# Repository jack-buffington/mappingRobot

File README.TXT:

This readme was last updated on March 20 2022.

This repository will eventually contain all of the files necessary to make a mapping robot that can map its 
environment using a 2D lidar-like sensor.  At the time of writing this README, the project is 
ongoing.  Eventual goals of this project are:

* Have the robot autonomously map its environment using a RPlidar A2 module.  
* Know when it is done mapping its environment. 
* Do so using ROS.  
* With only a few minor exceptions, run exclusively my own code.
* Have the capability to connect to the robot using a remote computer which can view the current state of the
map as well as to take direct control of the robot.  

The robot system will consist of three processors.  The first is the remote computer which does no 
major computation.  It will be for the user to view the map and to control the state of the robot if necessary.  
The second is an onboard processor that will do the heavy lifting and which holds 
the most up-to-date map.  The third is a microcontroller that handles low-level tasks such as driving the motors, 
reading sensors, and controllng the power to the motors, CPU, and itself. 

Power is supplied to the robot from an off-the-shelf battery pack for Dewalt cordless tools.  

It its current state, the MCU code is pretty much fully functional.  I will likely update it at some point to
read one or more downward-looking range finders so that it doesn't attempt suicide by driving down steps.  It currently
can do the following:
   * Read the battery voltage, display it on the OLED display, and send the voltage to the CPU
   * Read the encoders attached to the motors and send their values to the CPU
   * Drive the motors with a closed-loop velocity controller
   * Play beeps
   * Control the power to the CPU, motors, and itself
   * Communicate through two serial ports.  One to the CPU and one connected to the programming port.
  
The CPU code has:
   RPlidar node - controls a RPlidar A2 and reads its data.  This data is conditionally published based on a divider that 
       Allows it to send every N scans.  
   MCU node - Subscribes to a few topics which can be forwarded to the MCU and publishes a couple others which repeat 
       messages received from the MCU in a ROS-friendly format.  

The Remote computer code has:
   lidar viewer - Ideally I would use RVIZ to see the lidar data but either I don't yet know how to use RVIZ or I have it
	misconfigured so I wrote a quick and dirty program to display the scans.  
   joystick driving node - Lets you control the robot with a joystick if you have teleop_twist_joy installed on your system.

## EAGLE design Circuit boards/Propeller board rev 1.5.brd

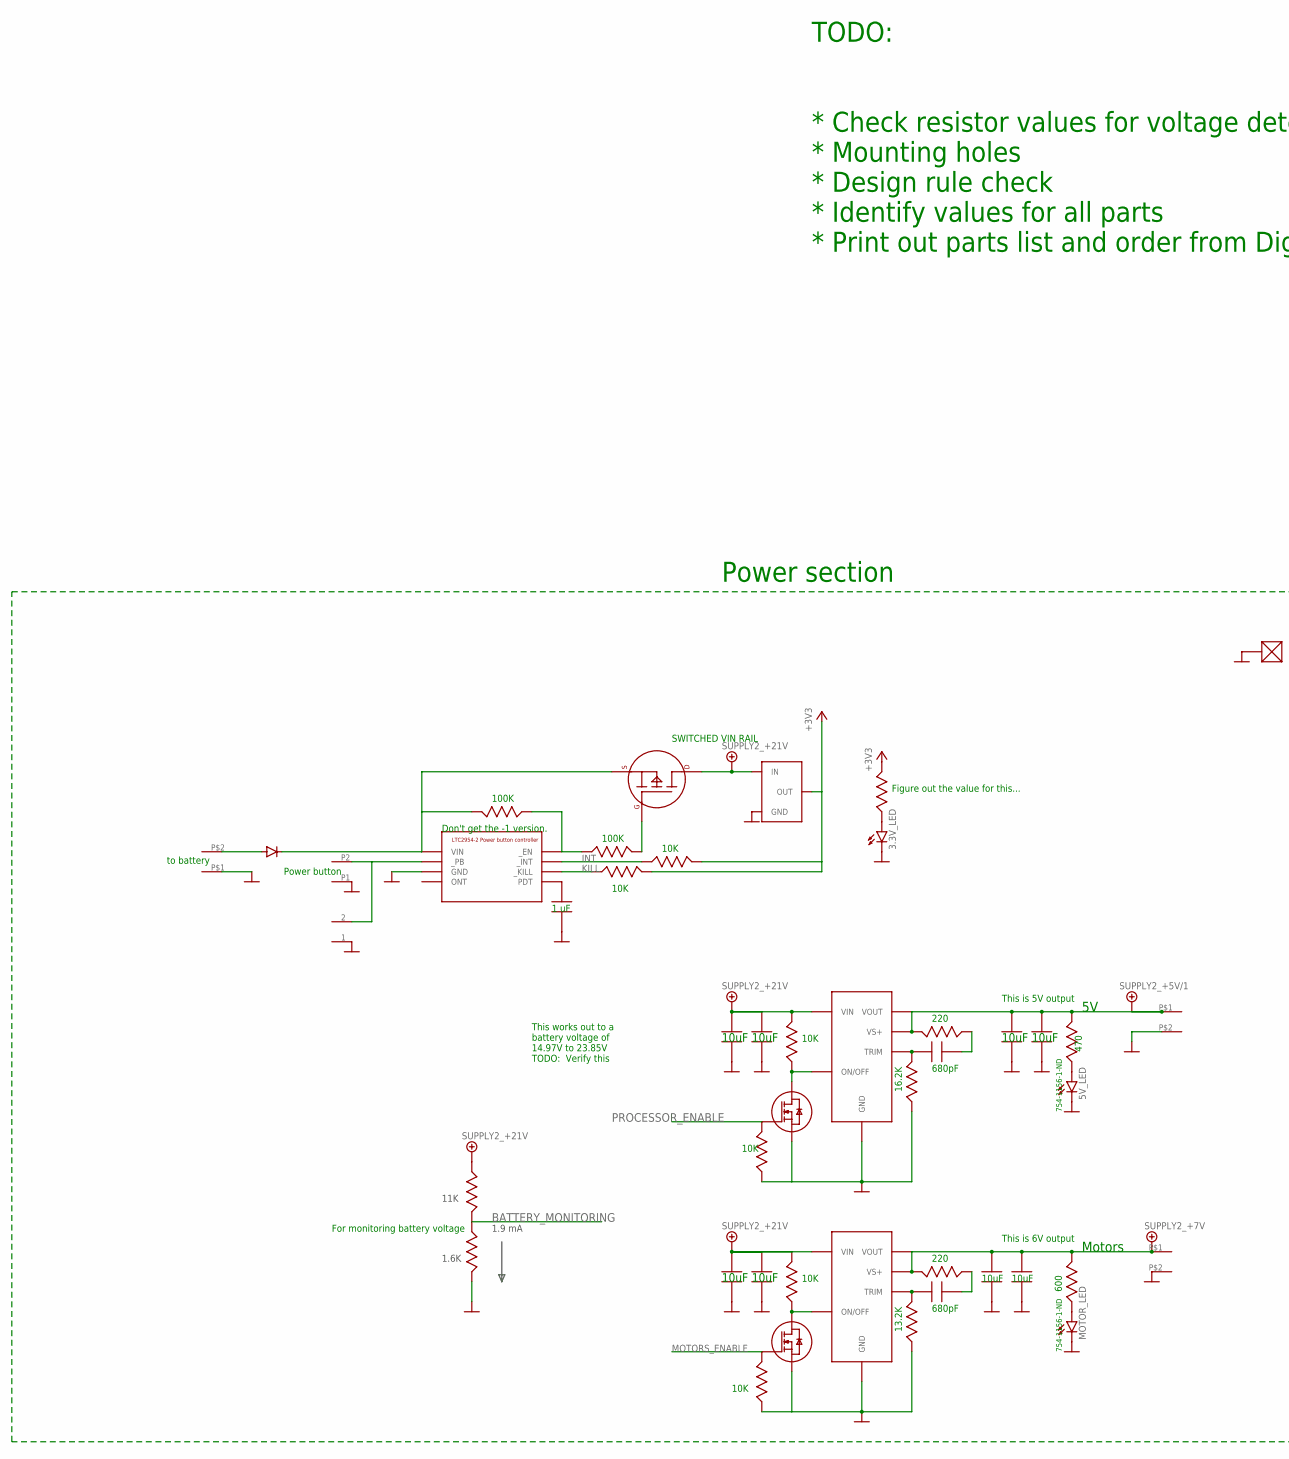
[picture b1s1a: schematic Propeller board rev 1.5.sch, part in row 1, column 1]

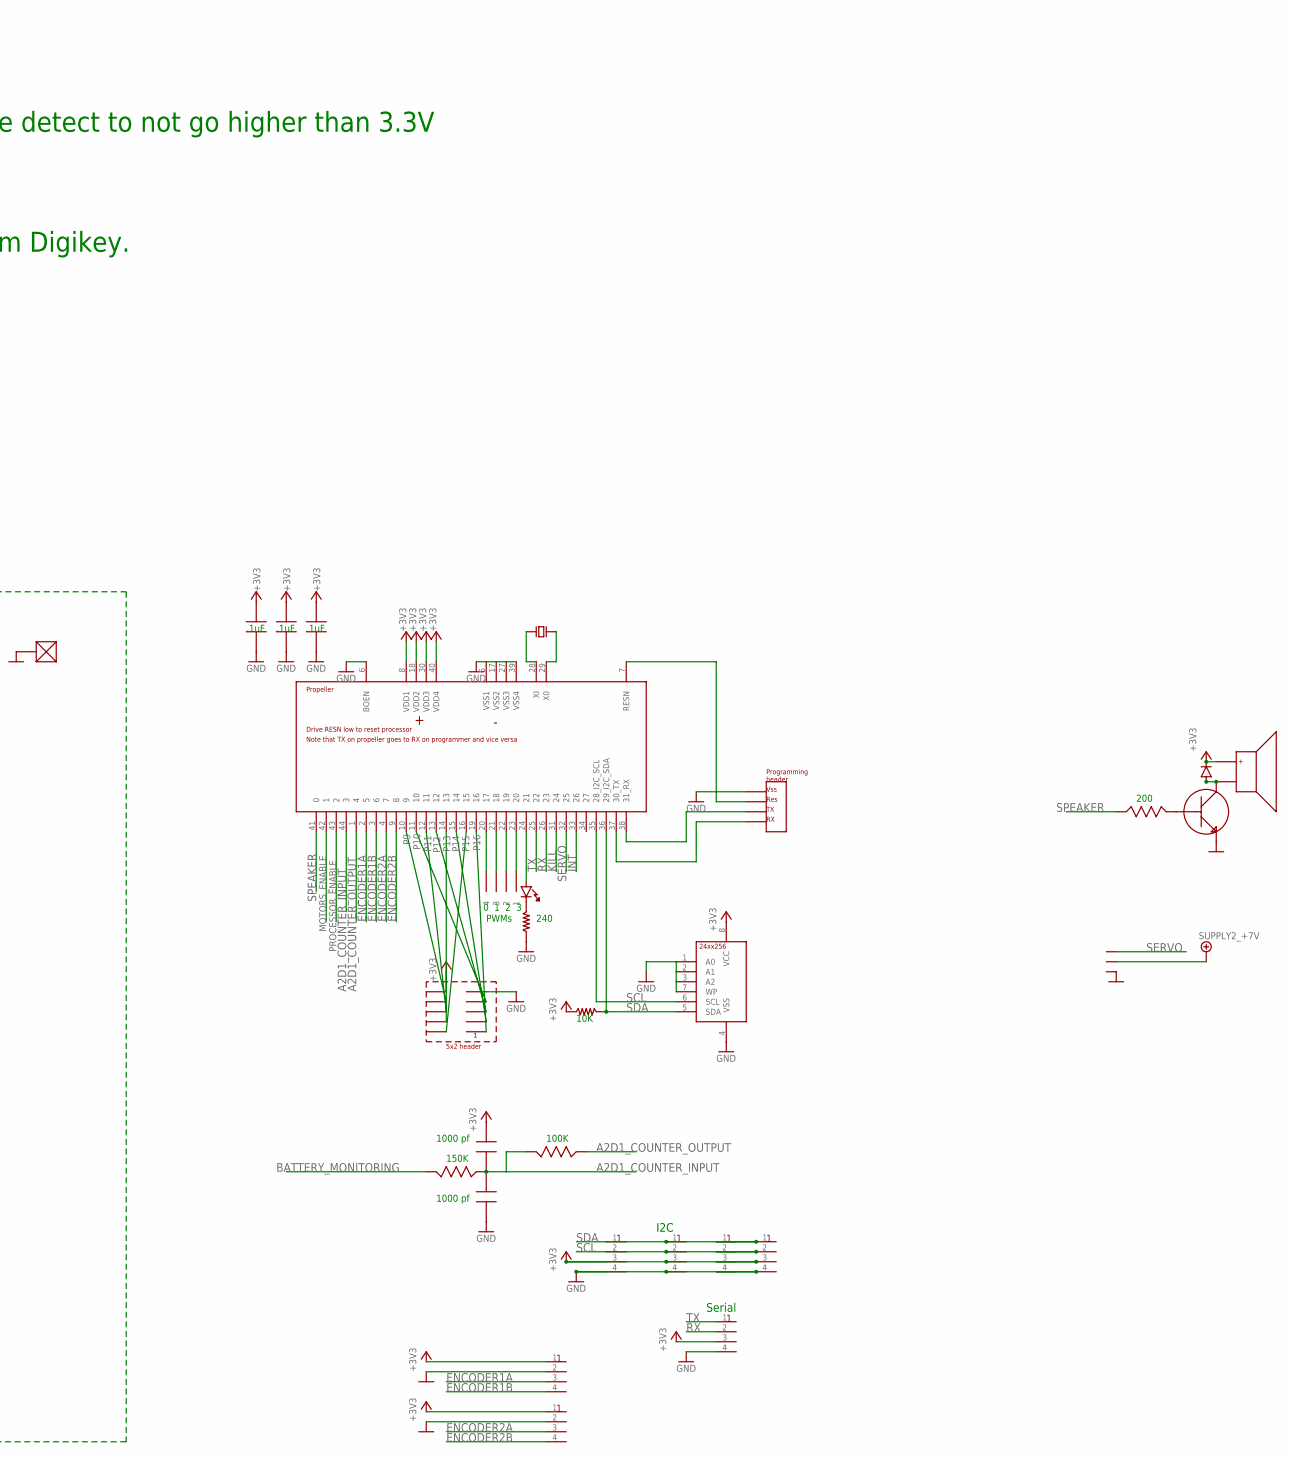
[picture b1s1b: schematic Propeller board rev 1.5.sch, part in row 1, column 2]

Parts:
3.3V_LED, 5V_LED: LED_LEDSML1206; LED_SML1206
3V3_REGULATOR_FOR_PROPELLER: VOLTAGE_REGULATOR_3_TERMINALXP_POWER_VR05_SERIES; VR05_SERIES_VREG
5V_C_680PF: 680pf; JACK_0805
5V_LED_R1, 5V_LED_R2: 470; JACK_0805
5V_REGULATOR_PULLUP: 10K; JACK_0805
5V_R_220: 220; JACK_0805
BATTERY_VOLTAGE_DIVIDER_HIGH: 11K; JACK_0805
BATTERY_VOLTAGE_DIVIDER_LOW: 1.6K; JACK_0805
MOTOR_C_680PF: 680pf; JACK_0805
MOTOR_ENABLE_MOSFET, MOTOR_ENABLE_MOSFET1: JACK_MOSFET_N_CHANNELBSS138LCT-ND; JACK_SOT23
MOTOR_LED: LED_LEDSML1206; LED_SML1206
MOTOR_LED_R: 600; JACK_0805
MOTOR_MOSFET_PULLDOWN: 10K; JACK_0805
MOTOR_PULLUP, MOTOR_PULLUP2: 10K; JACK_0805
MOTOR_R_220: 220; JACK_0805
MOTOR_TRIM: 13.2K; JACK_0805
R1: 240; 805_SMD
R25: 10k; 805_SMD
RTRIM_5V: 16.2K; JACK_0805
U1: PARALLAX_PROPELLER; 44LQFP
U2: EEPROM_24XX256; 8_MSOP
U$1: CONNECTOR_2_PINJST_PH_SERIES; JST_2_PIN_PH_SERIES
U$2, U$6, U$13: JACK_SCREW_TERMINAL_2_CONDUCTORAMP-282837-2; JACK_AMP-282837-2
U$3: POWER_CONTROLLER_LTC2954-2TSOT-23-8; TSOT-23-8
U$4, U$17: JACK_DC_TO_DC_VARIABLE_555-1172-1-ND; JACK_DC2DC_555-1172-1-ND
U$5: 1uf; 0805
U$7, U$9, U$44: 100K; 0805
U$10, U$27: 10K; 0805
U$11: 1000pF or 1nF; 0805
U$12: MOSFET_P_CHANNELSI4431CDY; SO8
U$14, U$16, U$18: .1uf; 0805
U$15: CRYSTAL8X4.5_PACKAGE; CRYSTAL_NX8045GB-5MHZ-STD-CSF-3
U$19: TEST_POINT; KEYSTONE_ELECTRONICS_5118_TEST_POINT
U$20: LED0805; 0805
U$21: HEADER_4_PIN_.1"; FOUR_.1"_HOLES
U$22: HEADER_5X2; HEADER_5X2_.1"_SPACING
U$23, U$24, U$25, U$45, U$46, U$47, U$49: CONNECTOR_4_PINJST_PH_SERIES; JST_4_PIN_PH_SERIES
U$26: CONNECTOR_2_PINJST_.1"; JST_2_PIN_.1"
U$28, U$29: 10uF; 1210
U$30, U$31, U$32, U$33, U$40, U$41: 10uf; 1210
U$34: SPEAKERGT-0950RP3; AUDIO_TRANSDUCER_GT-0950RP3
U$35: DIODESOD523F; SOD523F
U$36: TRANSISTOR_NPNMMBT3904; SOT23
U$37: 200; 0805
U$38: CONNECTOR_3_PIN.1"SPACING; THREE_.1"_HOLES
U$39: DIODEPOWER_DI15; POWER_DI15
U$42: 1000pf or 1 nF; 0805
U$43: 150K; 0805
U$48: PROPELLER_PROGRAMMING_HEADERHOLES; FOUR_.1"HOLES

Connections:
+3V3: 3V3_REGULATOR_FOR_PROPELLER.VOUT (OUT), 5V_LED_R2.P$3, R25.P$1, U1.8 (VDD1), U1.18 (VDD2), U1.30 (VDD3), U1.40 (VDD4), U2.8 (VCC), U$10.C2, U$11.C2 (2-), U$14.C2 (2-), U$16.C2 (2-), U$18.C2 (2-), U$22.P10 (10), U$23.3, U$24.3, U$25.3, U$27.C2, U$34.+, U$35.C, U$45.3, U$46.1, U$47.3, U$49.1
+5V/1: 5V_LED_R1.P$3, 5V_R_220.P$3, U$2.P$1, U$4.VOUT, U$4.VS+, U$30.2 (2-), U$33.2 (2-)
+7V: MOTOR_LED_R.P$3, MOTOR_R_220.P$3, U$13.P$1, U$17.VOUT, U$17.VS+, U$32.2 (2-), U$38.2, U$40.2 (2-)
+21V: 3V3_REGULATOR_FOR_PROPELLER.VIN (IN), 5V_REGULATOR_PULLUP.P$3, BATTERY_VOLTAGE_DIVIDER_HIGH.P$2, MOTOR_PULLUP.P$3, U$4.VIN, U$12.5 (D), U$12.6 (D), U$12.7 (D), U$12.8 (D), U$17.VIN, U$28.2 (2-), U$29.2 (2-), U$31.2 (2-), U$41.2 (2-)
A2D1_COUNTER_INPUT: U1.44 (3), U$11.A1 (1+), U$42.C2 (2-), U$43.A1, U$44.C2
A2D1_COUNTER_OUTPUT: U1.1 (4), U$44.A1
BATTERY_MONITORING: BATTERY_VOLTAGE_DIVIDER_HIGH.P$3, BATTERY_VOLTAGE_DIVIDER_LOW.P$2, U$43.C2
ENCODER1A: U1.2 (5), U$46.3
ENCODER1B: U1.3 (6), U$46.4
ENCODER2A: U1.4 (7), U$49.3
ENCODER2B: U1.9 (8), U$49.4
GND: 3.3V_LED.C, 3V3_REGULATOR_FOR_PROPELLER.GND, 5V_LED.C, BATTERY_VOLTAGE_DIVIDER_LOW.P$3, MOTOR_ENABLE_MOSFET.2 (S), MOTOR_ENABLE_MOSFET1.2 (S), MOTOR_LED.C, MOTOR_MOSFET_PULLDOWN.P$2, MOTOR_PULLUP2.P$2, MOTOR_TRIM.P$2, R1.P$1, RTRIM_5V.P$2, U1.5 (VSS1), U1.6 (BOEN), U1.17 (VSS2), U1.27 (VSS3), U1.39 (VSS4), U2.1 (A0), U2.2 (A1), U2.3 (A2), U2.4 (VSS), U2.7 (WP), U$1.P1, U$2.P$2, U$3.4 (GND), U$4.GND, U$5.A1 (1+), U$6.P$1, U$13.P$2, U$14.A1 (1+), U$16.A1 (1+), U$17.GND, U$18.A1 (1+), U$19.P1, U$22.P9 (9), U$23.4, U$24.4, U$25.4, U$26.1, U$28.1 (1+), U$29.1 (1+), U$30.1 (1+), U$31.1 (1+), U$32.1 (1+), U$33.1 (1+), U$36.2 (E), U$38.1, U$40.1 (1+), U$41.1 (1+), U$42.A1 (1+), U$45.4, U$46.2, U$47.4, U$48.1 (VSS), U$49.2
INT: U1.33 (26), U$3.5 (_INT), U$10.A1
KILL: U1.31 (24), U$3.8 (_KILL), U$27.A1
MOTORS_ENABLE: MOTOR_ENABLE_MOSFET.1 (G), MOTOR_MOSFET_PULLDOWN.P$3, U1.42 (1)
unnamed: U1.7 (RESN), U$48.2 (RES)
unnamed: U1.24 (21), U$20.A1 (A)
unnamed: U$1.P2, U$3.2 (_PB), U$26.2
unnamed: MOTOR_LED.A, MOTOR_LED_R.P$2
unnamed: U$3.1 (VIN), U$7.C2, U$12.1 (S), U$12.2 (S), U$12.3 (S), U$39.3 (C)
unnamed: U$3.7 (PDT), U$5.C2 (2-)
unnamed: U$3.6 (_EN), U$7.A1, U$9.A1
unnamed: MOTOR_ENABLE_MOSFET.3 (D), MOTOR_PULLUP.P$2, U$17.ON/OFF
unnamed: U$9.C2, U$12.4 (G)
unnamed: R1.P$2, U$20.C2 (C)
unnamed: U1.23 (20), U$21.1
unnamed: U1.22 (19), U$21.2
unnamed: U1.21 (18), U$21.3
unnamed: U$34.-, U$35.A, U$36.3 (C)
unnamed: U$36.1 (B), U$37.C2
unnamed: U1.20 (17), U$21.4
unnamed: 5V_C_680PF.P$3 (2), RTRIM_5V.P$3, U$4.TRIM
unnamed: 3.3V_LED.A, 5V_LED_R2.P$2
unnamed: U$6.P$2, U$39.1 (A), U$39.2 (A)
unnamed: U1.38 (31_RX), U$48.3 (TX)
unnamed: 5V_LED.A, 5V_LED_R1.P$2
unnamed: 5V_REGULATOR_PULLUP.P$2, MOTOR_ENABLE_MOSFET1.3 (D), U$4.ON/OFF
unnamed: 5V_C_680PF.P$2 (1), 5V_R_220.P$2
unnamed: MOTOR_C_680PF.P$3 (2), MOTOR_TRIM.P$3, U$17.TRIM
unnamed: MOTOR_C_680PF.P$2 (1), MOTOR_R_220.P$2
unnamed: U1.37 (30_TX), U$48.4 (RX)
unnamed: U1.28 (XI), U$15.1
unnamed: U1.29 (X0), U$15.2
P9: U1.10 (9), U$22.P8 (8)
P10: U1.11 (10), U$22.P7 (7)
P11: U1.12 (11), U$22.P6 (6)
P12: U1.13 (12), U$22.P5 (5)
P13: U1.14 (13), U$22.P4 (4)
P14: U1.15 (14), U$22.P3 (3)
P15: U1.16 (15), U$22.P2 (2)
P16: U1.19 (16), U$22.P1 (1)
PROCESSOR_ENABLE: MOTOR_ENABLE_MOSFET1.1 (G), MOTOR_PULLUP2.P$3, U1.43 (2)
RX: U1.26 (23), U$47.2
SCL: U1.35 (28_I2C_SCL), U2.6 (SCL), U$23.2, U$24.2, U$25.2, U$45.2
SDA: R25.P$2, U1.36 (29_I2C_SDA), U2.5 (SDA), U$23.1, U$24.1, U$25.1, U$45.1
SERVO: U1.32 (25), U$38.3
SPEAKER: U1.41 (0), U$37.A1
TX: U1.25 (22), U$47.1

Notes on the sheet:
to battery
For monitoring battery voltage
Motors
Power section
754-1156-1-ND
11K
1.6K
1.9 mA
This works out to a battery voltage of 14.97V to 23.85V TODO: Verify this
Power button
10K
This is 6V output
This is 5V output
13.2K
16.2K
220
680pF
470
600
SWITCHED VIN RAIL
100K
TODO: * Check resistor values for voltage detect to not go higher than 3.3V * Mounting holes * Design rule check * Identify values for all parts * Print out parts list and order from Digikey.
10uF
I2C
Serial
PWMs
150K
Figure out the value for this...
0 1 2 3
1000 pf
240
200
1 uF
.1uF
Don't get the -1 version.

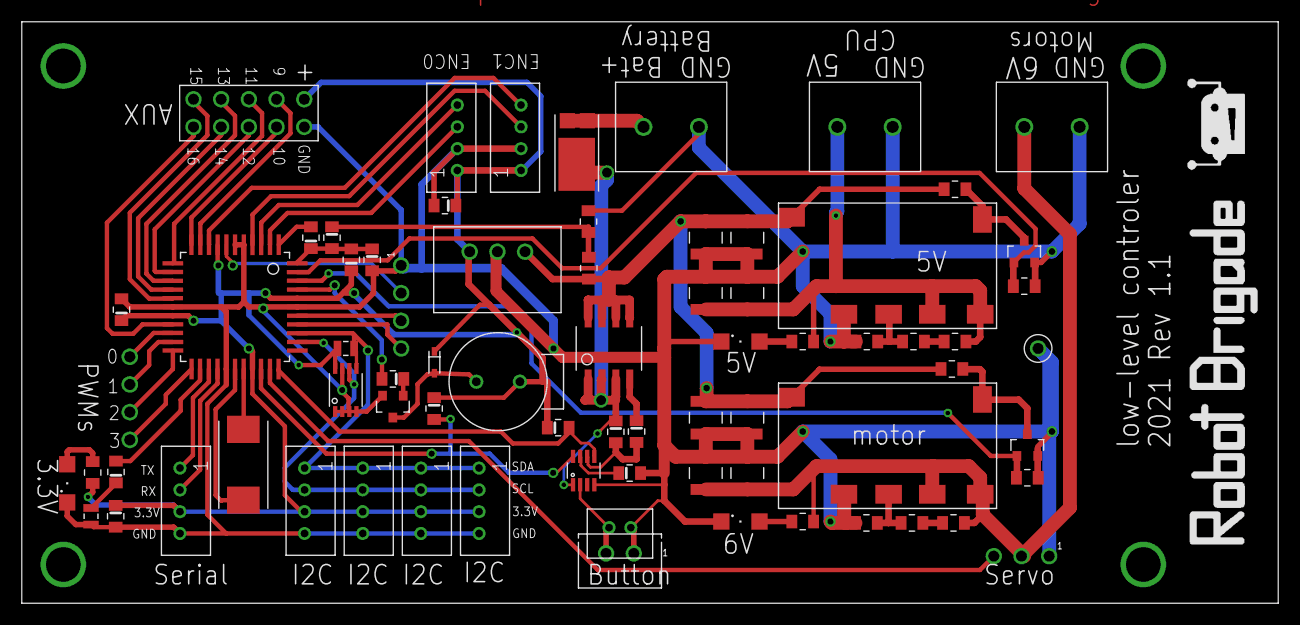
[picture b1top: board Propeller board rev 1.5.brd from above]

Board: 2 copper layers, 115.2 x 53.3 mm, 74 parts (0 on the bottom side), 58 nets.

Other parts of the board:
U$8: ROBOT_BRIGADE_LOGO_AND_TEXT_.2"

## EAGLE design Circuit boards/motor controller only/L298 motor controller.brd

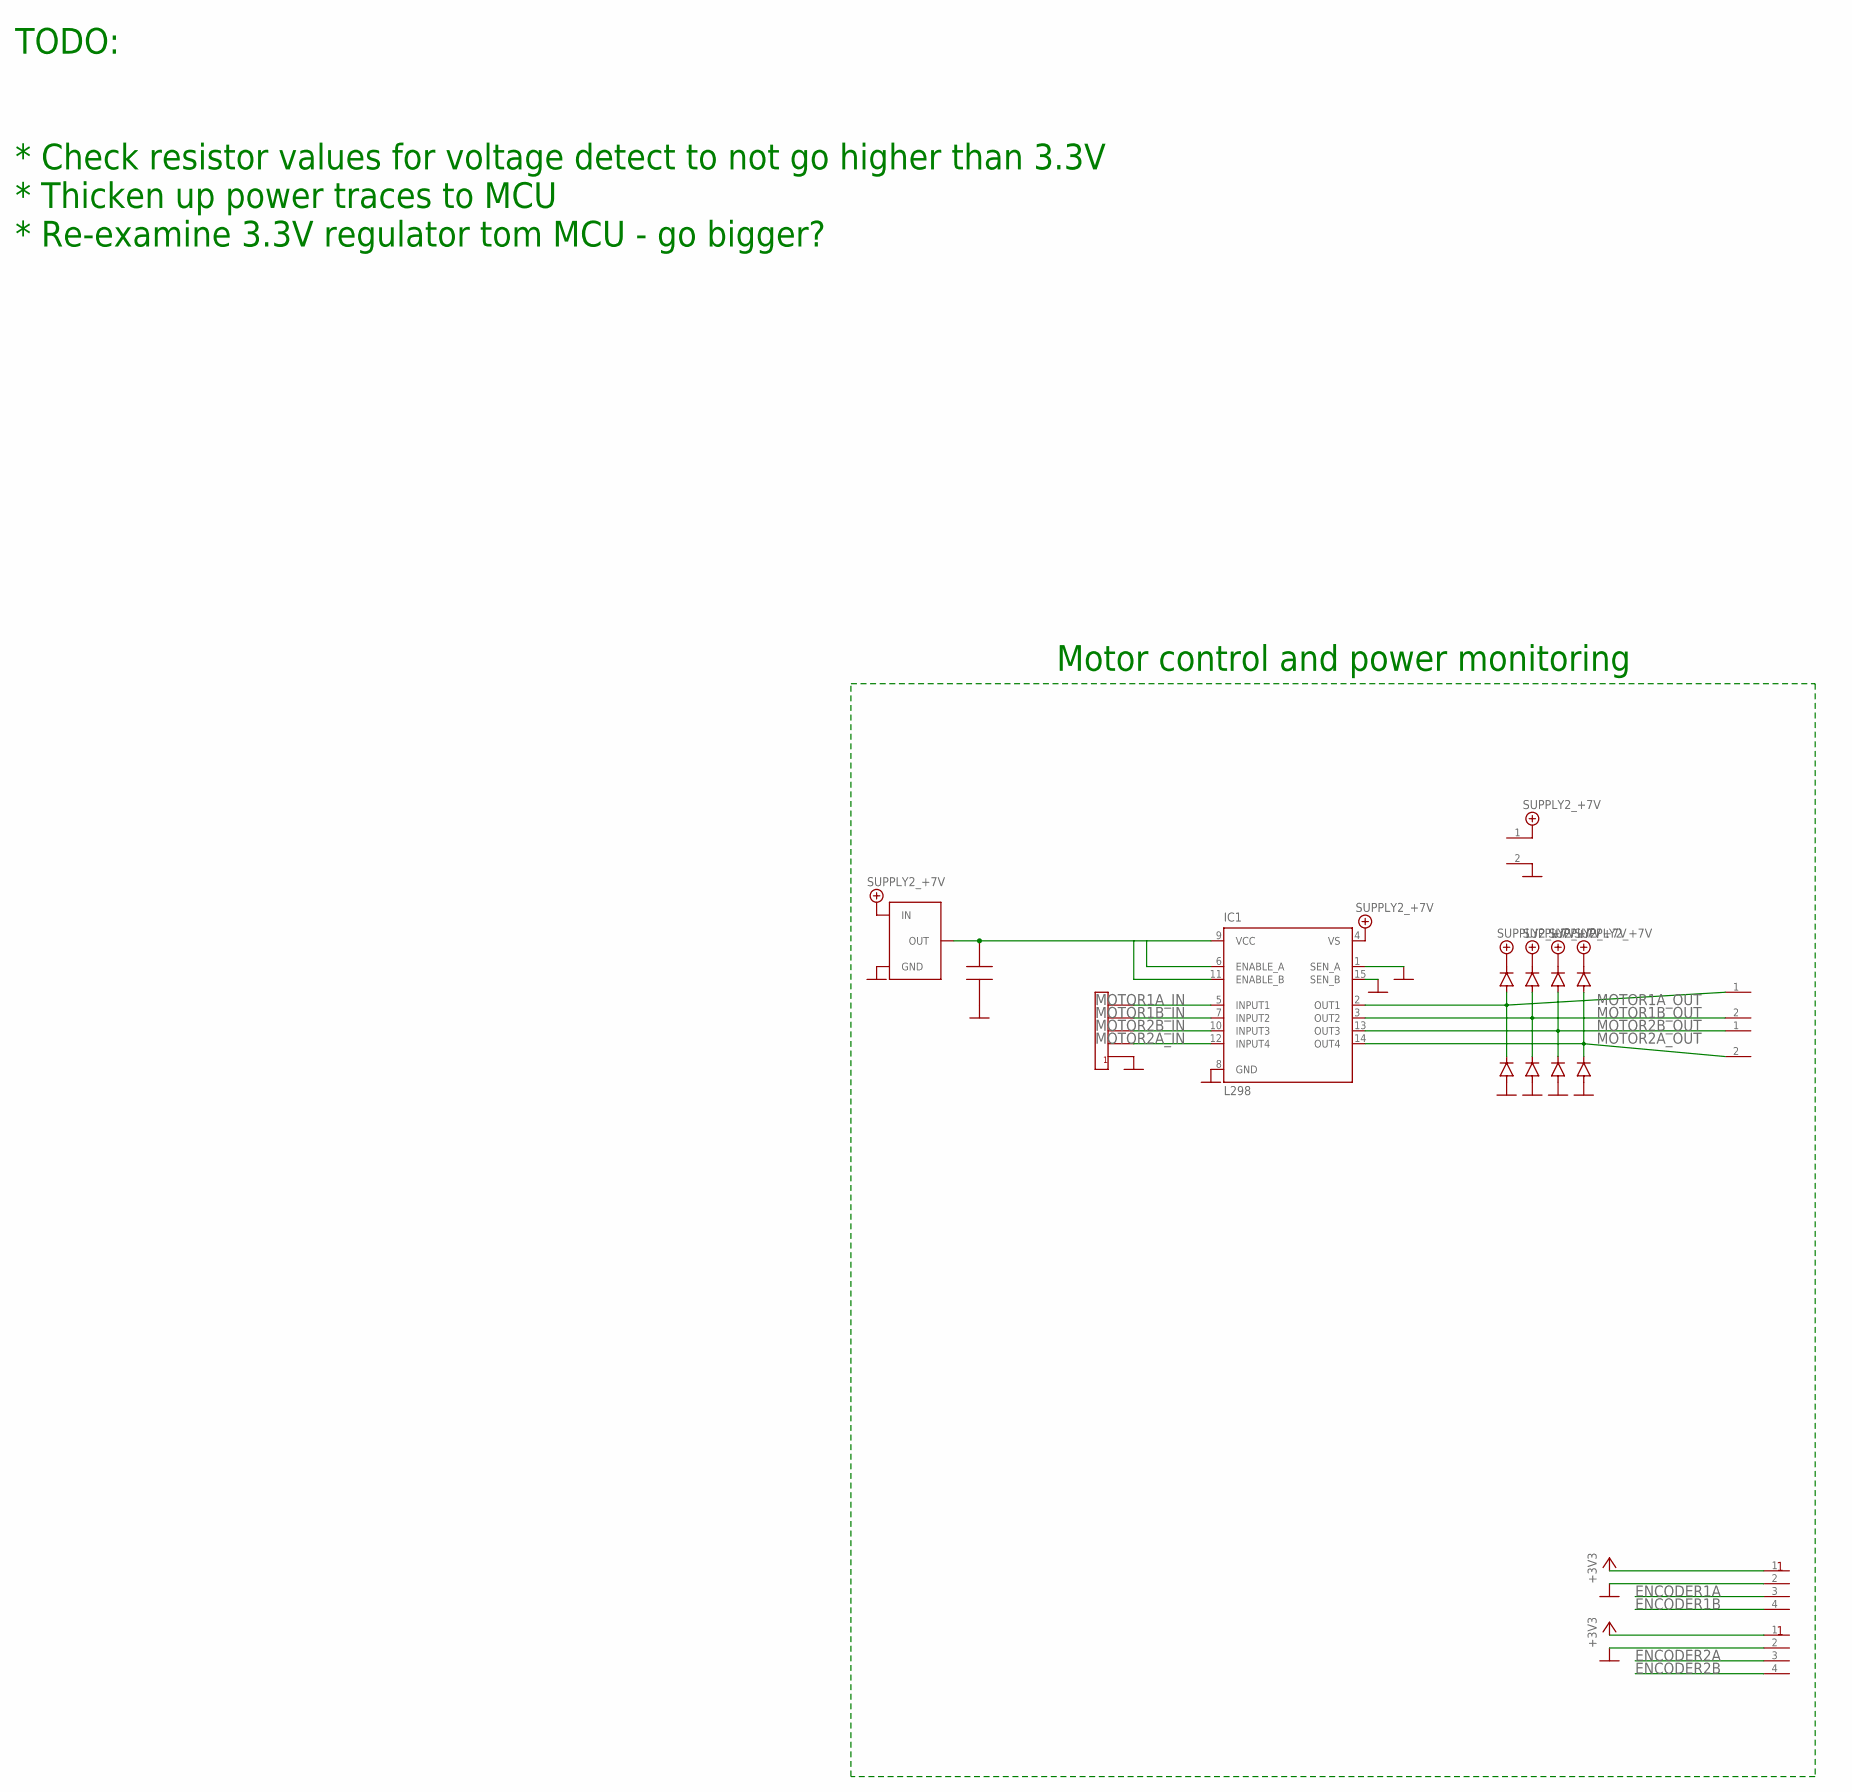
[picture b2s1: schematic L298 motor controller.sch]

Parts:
IC1: L298; MULTIWATT-15
U$1, U$2, U$4: SCREW_TERMINAL_2_CONDUCTOR_M20109-ND; WM20109-ND
U$3: CONNECTOR_5_PIN; JST_5_PIN_PH_SERIES
U$13, U$14, U$16, U$18, U$19, U$20, U$21, U$22: DIODESOD-123FL; SOD-123FL
U$25: VOLTAGE_REGULATOR_3_TERMINALMCP1799_SOT23; SOT23
U$26: CAPACITOR0805; 0805
U$46, U$49: CONNECTOR_4_PINJST_PH_SERIES; JST_4_PIN_PH_SERIES

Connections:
+3V3: U$46.1, U$49.1
+7V: IC1.4 (VS), U$13.C, U$14.C, U$16.C, U$18.C, U$25.3 (IN)
ENCODER1A: U$46.3
ENCODER1B: U$46.4
ENCODER2A: U$49.3
ENCODER2B: U$49.4
GND: IC1.1 (SEN_A), IC1.8 (GND), IC1.15 (SEN_B), U$3.1, U$19.A, U$20.A, U$21.A, U$22.A, U$25.1 (GND), U$26.P$2 (1+), U$46.2, U$49.2
MOTOR1A_IN: IC1.5 (INPUT1), U$3.5
MOTOR1A_OUT: IC1.2 (OUT1), U$1.1, U$13.A, U$19.C
MOTOR1B_IN: IC1.7 (INPUT2), U$3.4
MOTOR1B_OUT: IC1.3 (OUT2), U$1.2, U$14.A, U$20.C
MOTOR2A_IN: IC1.12 (INPUT4), U$3.2
MOTOR2A_OUT: IC1.14 (OUT4), U$2.2, U$18.A, U$22.C
MOTOR2B_IN: IC1.10 (INPUT3), U$3.3
MOTOR2B_OUT: IC1.13 (OUT3), U$2.1, U$16.A, U$21.C
unnamed: IC1.6 (ENABLE_A), IC1.9 (VCC), IC1.11 (ENABLE_B), U$25.2 (OUT), U$26.P$3 (2-)

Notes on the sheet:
Motor control and power monitoring
TODO: * Check resistor values for voltage detect to not go higher than 3.3V * Thicken up power traces to MCU * Re-examine 3.3V regulator tom MCU - go bigger?

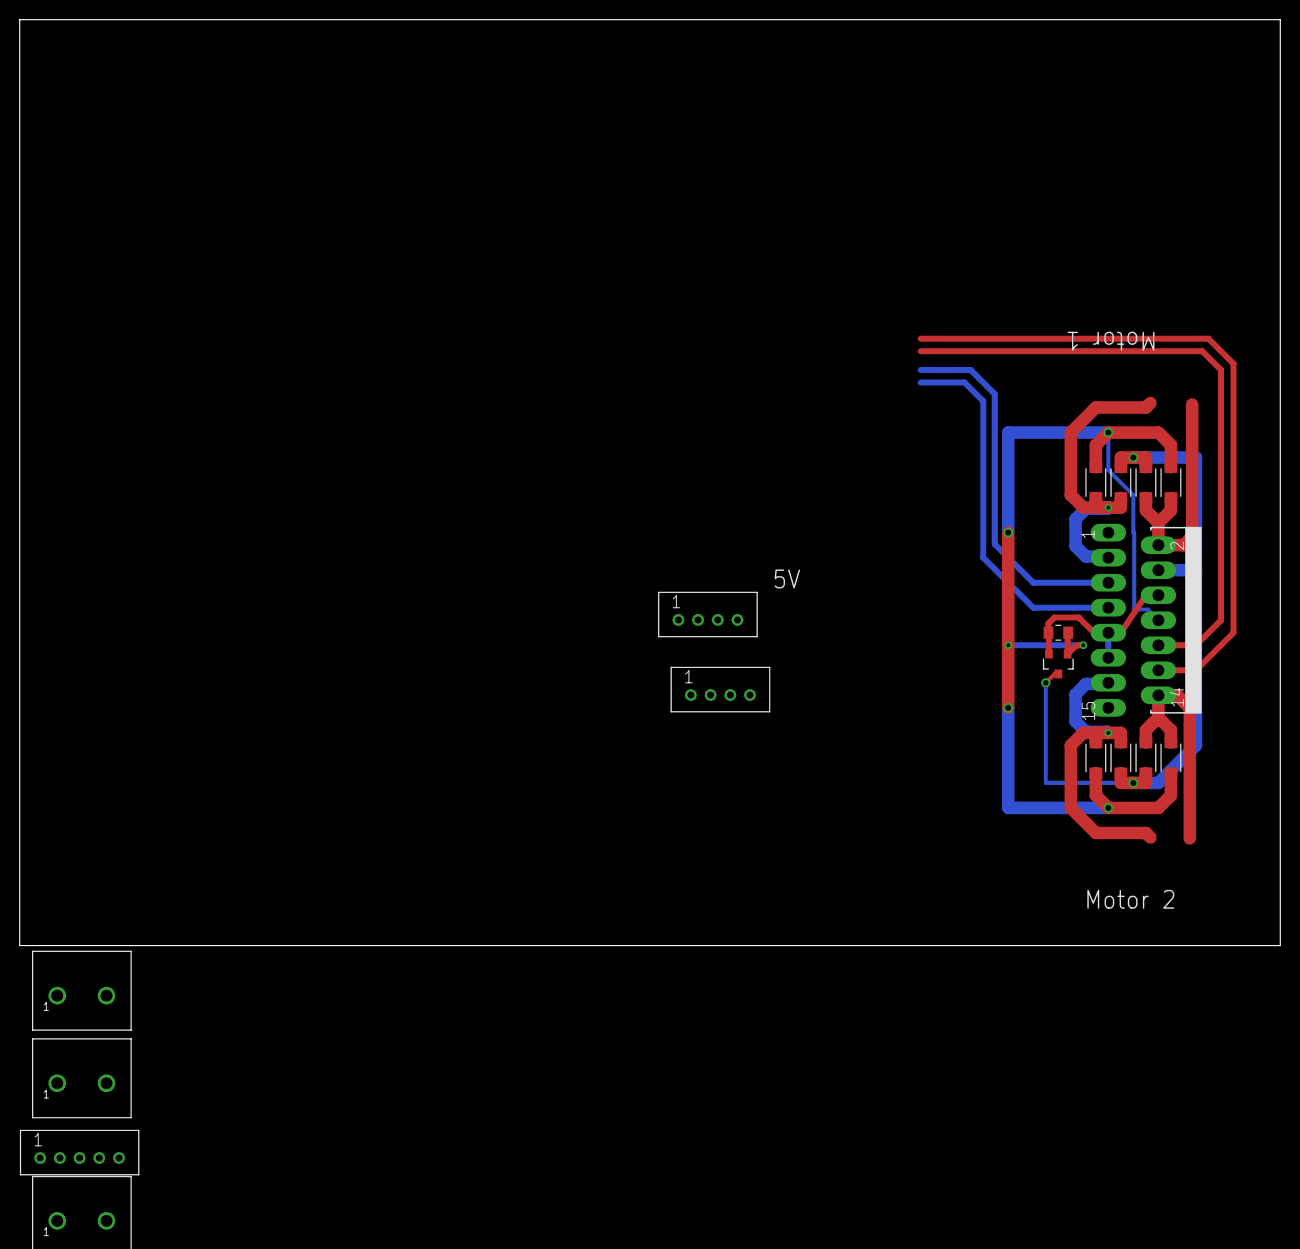
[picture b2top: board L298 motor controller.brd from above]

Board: 2 copper layers, 127.9 x 94.0 mm, 17 parts (0 on the bottom side), 12 nets.

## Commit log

2019-08-08 added readme
2019-08-11 Fixed tiny error
2019-08-12 Now successfully finding the robot on the network!
2019-08-13 Modified the code to search IP addresses in four chunks
2019-08-13 findAllRobots now gives a serial number with the IP address in a robotIP struct
2021-09-21 Cleaned away very old stuff to make way for the new stuff
2021-09-21 Initial commit of new code and files.
2021-10-17 initial commit of ROS package containing MCUnode
2021-10-17 deleted some files but Windows is being overly broad when doing git rm...
2021-10-17 Moved the class definition to the .hpp file.
2021-11-12 Updated with hopefully good instructions for compiliation
2021-11-12 slight tweak to MCU node.
2021-11-12 cleaned up the MCU files.
2021-11-13 Adding a manual control node.
2021-11-14 Now the manual driving node works!
2021-11-14 Added a couple of faster driving speeds.
2021-11-16 Switched from string to float[] for driveMotors
2021-11-27 Added jack_test package, which has an example of making a custom message in it.
2021-12-04 initial rplidar node - not functional yet but compiles.
2021-12-05 Actually added things this time...
2021-12-21 rplidar node is now working with the express scan mode! Code still needs to be cleaned up.
2022-01-10 Launch file works but not on boot yet.
2022-01-10 Add encoder message
2022-01-10 Rebuild the dev_ws directory.
2022-01-10 updated a copy/paste but that was causing the rplidar node to identify as a mcu node.
2022-03-06 Resored beep functionality.
2022-03-20 Add remote computer code
2022-03-20 update mcuNode
2022-03-21 Update documentation
2022-03-21 Add straggler files that weren't in the repository
2022-03-28 clean up files
2022-04-06 Clean directory
2022-04-11 Fix joystick driving issue
